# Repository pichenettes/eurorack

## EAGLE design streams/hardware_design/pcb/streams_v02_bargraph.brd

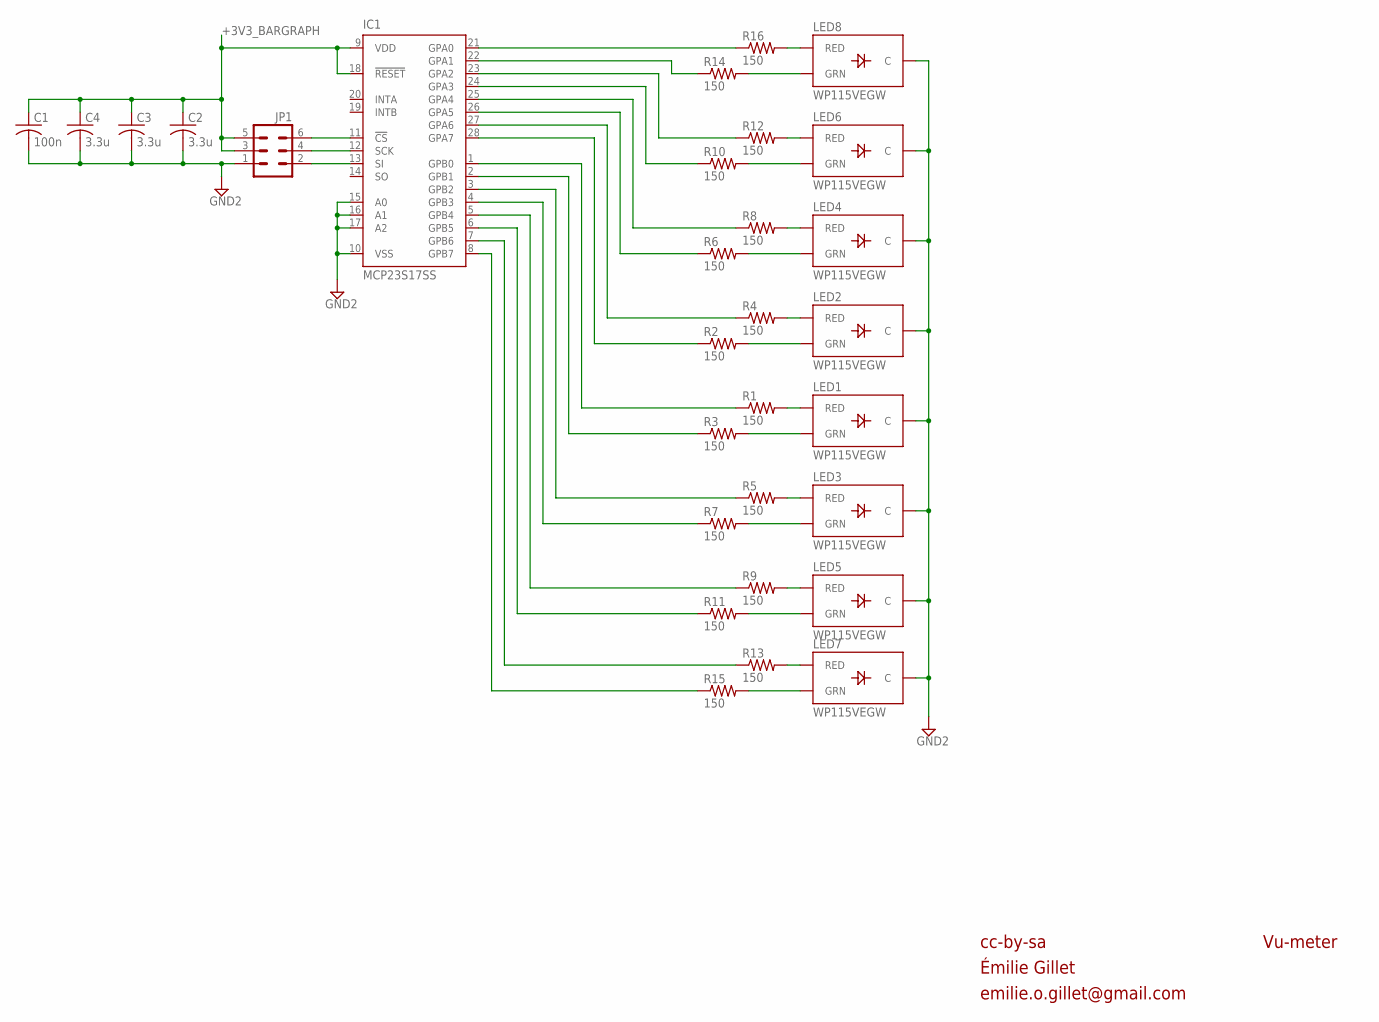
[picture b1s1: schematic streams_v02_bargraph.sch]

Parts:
C1: 100n; C0603
C2, C3, C4: 3.3u; C0603
IC1: MCP23S17SS; SSOP28
JP1: M03X2; 2X3
LED1, LED2, LED3, LED4, LED5, LED6, LED7, LED8: WP115VEGW; LED-BICOLOR-THROUGHHOLE
R1, R2, R3, R4, R5, R6, R7, R8, R9, R10, R11, R12, R13, R14, R15, R16: 150; R0603

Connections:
+3V3_BARGRAPH: C1.1, C2.1, C3.1, C4.1, IC1.9 (VDD), IC1.18 (!RESET), JP1.3, JP1.5
GND2: C1.2, C2.2, C3.2, C4.2, IC1.10 (VSS), IC1.15 (A0), IC1.16 (A1), IC1.17 (A2), JP1.1, LED1.2 (C), LED2.2 (C), LED3.2 (C), LED4.2 (C), LED5.2 (C), LED6.2 (C), LED7.2 (C), LED8.2 (C)
unnamed: IC1.11 (!CS), JP1.6
unnamed: IC1.12 (SCK), JP1.4
unnamed: LED1.3 (RED), R1.2
unnamed: IC1.13 (SI), JP1.2
unnamed: LED1.1 (GRN), R3.2
unnamed: LED3.3 (RED), R5.2
unnamed: LED3.1 (GRN), R7.2
unnamed: LED5.3 (RED), R9.2
unnamed: LED5.1 (GRN), R11.2
unnamed: LED7.3 (RED), R13.2
unnamed: LED7.1 (GRN), R15.2
unnamed: LED8.3 (RED), R16.2
unnamed: LED8.1 (GRN), R14.2
unnamed: LED6.3 (RED), R12.2
unnamed: LED6.1 (GRN), R10.2
unnamed: LED4.3 (RED), R8.2
unnamed: LED4.1 (GRN), R6.2
unnamed: LED2.3 (RED), R4.2
unnamed: LED2.1 (GRN), R2.2
unnamed: IC1.27 (GPA6), R4.1
unnamed: IC1.28 (GPA7), R2.1
unnamed: IC1.1 (GPB0), R1.1
unnamed: IC1.2 (GPB1), R3.1
unnamed: IC1.21 (GPA0), R16.1
unnamed: IC1.22 (GPA1), R14.1
unnamed: IC1.23 (GPA2), R12.1
unnamed: IC1.24 (GPA3), R10.1
unnamed: IC1.25 (GPA4), R8.1
unnamed: IC1.26 (GPA5), R6.1
unnamed: IC1.3 (GPB2), R5.1
unnamed: IC1.4 (GPB3), R7.1
unnamed: IC1.5 (GPB4), R9.1
unnamed: IC1.6 (GPB5), R11.1
unnamed: IC1.7 (GPB6), R13.1
unnamed: IC1.8 (GPB7), R15.1

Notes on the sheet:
cc-by-sa
Vu-meter
Émilie Gillet
emilie.o.gillet@gmail.com

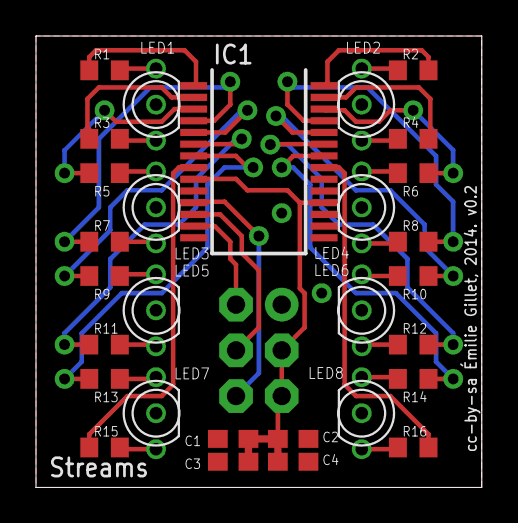
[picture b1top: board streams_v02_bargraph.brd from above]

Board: 2 copper layers, 24.8 x 25.1 mm, 30 parts (1 on the bottom side), 37 nets.

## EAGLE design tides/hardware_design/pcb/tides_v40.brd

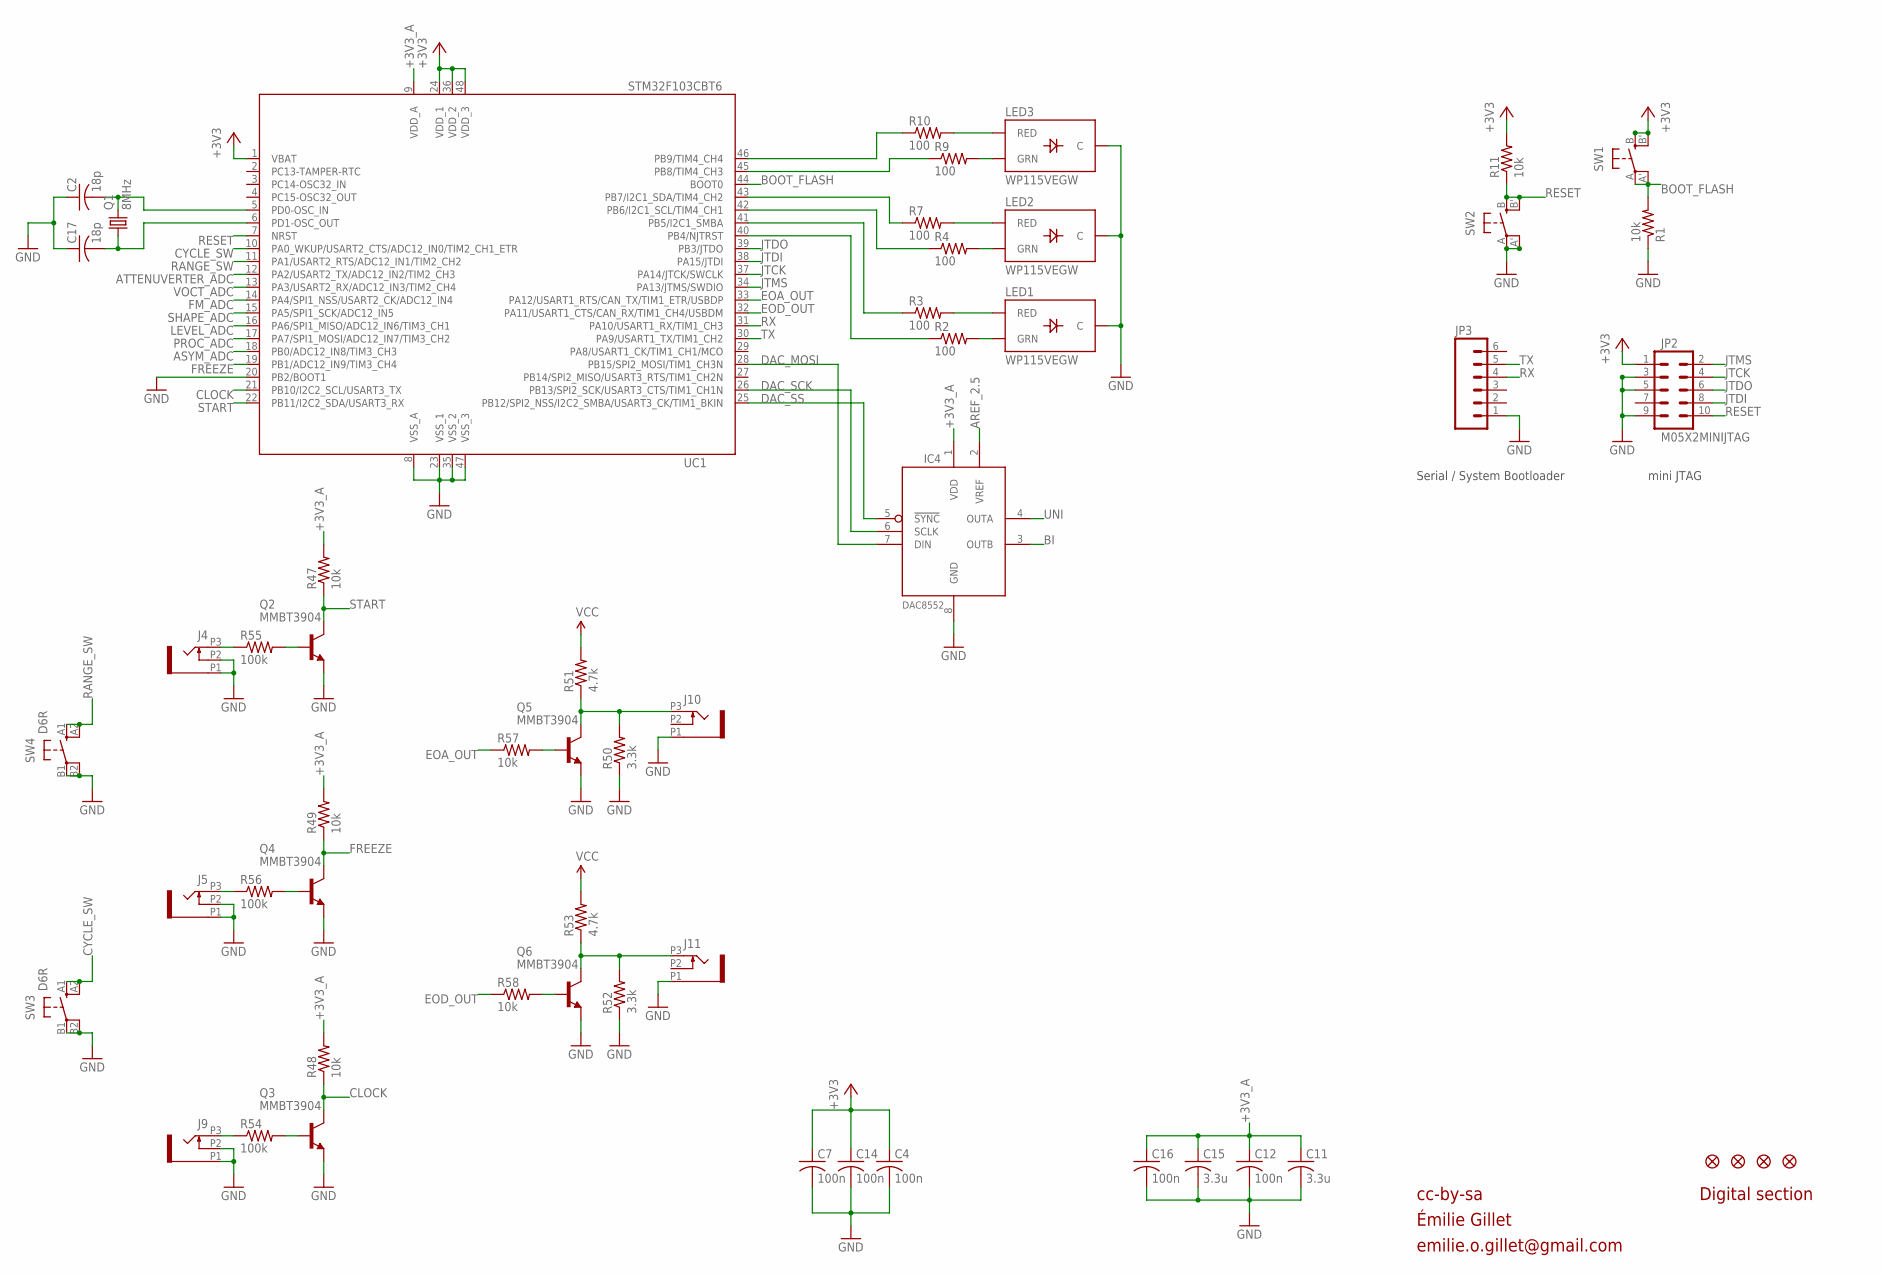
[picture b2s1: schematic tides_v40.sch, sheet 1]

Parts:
C2, C17: 18p; C0603
C4, C7, C12, C14, C16: 100n; C0603
C11, C15: 3.3u; C0603
IC4: DAC8552; MSOP-8
J4, J5, J9, J10, J11: PJ301_THONKICONN6; WQP_PJ_301M6
JP2: M05X2MINIJTAG; 2X5-1.27
JP3: M06SIP; 1X06
JP4, JP5, JP6, JP7: FIDUCIAL1X2; FIDUCIAL-1X2
LED1, LED2, LED3: WP115VEGW; LED-BICOLOR-THROUGHHOLE
Q1: 8MHz; HC49UP
Q2, Q3, Q4, Q5, Q6: MMBT3904; SOT23-BEC
R1, R11, R47, R48, R49, R57, R58: 10k; R0603
R2, R3, R4, R7, R9, R10: 100; R0603
R50, R52: 3.3k; R0603
R51, R53: 4.7k; R0603
R54, R55, R56: 100k; R0603
SW1, SW2: EVQQ2; EVQ-Q2
SW3, SW4: D6R
UC1: STM32F103CBT6; LQFP48

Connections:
+3V3: C4.1, C7.1, C14.1, JP2.1, R11.2, SW1.B (S), SW1.B' (S1), UC1.1 (VBAT), UC1.24 (VDD_1), UC1.36 (VDD_2), UC1.48 (VDD_3); also elsewhere on the board
+3V3_A: C11.1, C12.1, C15.1, C16.1, IC4.1 (VDD), R47.2, R48.2, R49.2, UC1.9 (VDD_A); also elsewhere on the board
AREF_2.5: IC4.2 (VREF); also elsewhere on the board
ASYM_ADC: UC1.18 (PB0/ADC12_IN8/TIM3_CH3); also elsewhere on the board
ATTENUVERTER_ADC: UC1.12 (PA2/USART2_TX/ADC12_IN2/TIM2_CH3); also elsewhere on the board
BI: IC4.3 (OUTB); also elsewhere on the board
BOOT_FLASH: R1.2, SW1.A, SW1.A' (P1), UC1.44 (BOOT0)
CLOCK: Q3.C, R48.1, UC1.21 (PB10/I2C2_SCL/USART3_TX)
CYCLE_SW: SW3.A1 (S), SW3.A2 (S1), UC1.10 (PA0_WKUP/USART2_CTS/ADC12_IN0/TIM2_CH1_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)
DAC_MOSI: IC4.7 (DIN), UC1.28 (PB15/SPI2_MOSI/TIM1_CH3N)
DAC_SCK: IC4.6 (SCLK), UC1.26 (PB13/SPI2_SCK/USART3_CTS/TIM1_CH1N)
DAC_SS: IC4.5 (!SYNC), UC1.25 (PB12/SPI2_NSS/I2C2_SMBA/USART3_CK/TIM1_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)
EOA_OUT: R57.1, UC1.33 (PA12/USART1_RTS/CAN_TX/TIM1_ETR/USBDP)
EOD_OUT: R58.1, UC1.32 (PA11/USART1_CTS/CAN_RX/TIM1_CH4/USBDM)
FM_ADC: UC1.14 (PA4/SPI1_NSS/USART2_CK/ADC12_IN4); also elsewhere on the board
FREEZE: Q4.C, R49.1, UC1.19 (PB1/ADC12_IN9/TIM3_CH4)
GND: C2.1, C4.2, C7.2, C11.2, C12.2, C14.2, C15.2, C16.2, C17.1, IC4.8 (GND), J4.P1 (1), J4.P2 (2), J5.P1 (1), J5.P2 (2), J9.P1 (1), J9.P2 (2), J10.P1 (1), J11.P1 (1), JP2.3, JP2.5, JP2.9, JP3.1, LED1.2 (C), LED2.2 (C), LED3.2 (C), Q2.E, Q3.E, Q4.E, Q5.E, Q6.E, R1.1, R50.1, R52.1, SW2.A, SW2.A' (P1), SW3.B1, SW3.B2 (P1), SW4.B1, SW4.B2 (P1), UC1.8 (VSS_A), UC1.20 (PB2/BOOT1), UC1.23 (VSS_1), UC1.35 (VSS_2), UC1.47 (VSS_3); also elsewhere on the board
JTCK: JP2.4, UC1.37 (PA14/JTCK/SWCLK)
JTDI: JP2.8, UC1.38 (PA15/JTDI)
JTDO: JP2.6, UC1.39 (PB3/JTDO)
JTMS: JP2.2, UC1.34 (PA13/JTMS/SWDIO)
LEVEL_ADC: UC1.16 (PA6/SPI1_MISO/ADC12_IN6/TIM3_CH1); also elsewhere on the board
unnamed: C2.2, Q1.2, UC1.5 (PD0-OSC_IN)
unnamed: C17.2, Q1.1, UC1.6 (PD1-OSC_OUT)
unnamed: J5.P3 (3), R56.1
unnamed: Q4.B, R56.2
unnamed: J9.P3 (3), R54.1
unnamed: Q3.B, R54.2
unnamed: Q6.B, R58.2
unnamed: J11.P3 (3), Q6.C, R52.2, R53.1
unnamed: LED3.3 (RED), R10.2
unnamed: LED3.1 (GRN), R9.2
unnamed: LED2.3 (RED), R7.2
unnamed: LED2.1 (GRN), R4.2
unnamed: LED1.3 (RED), R3.2
unnamed: LED1.1 (GRN), R2.2
unnamed: R10.1, UC1.46 (PB9/TIM4_CH4)
unnamed: R9.1, UC1.45 (PB8/TIM4_CH3)
unnamed: R7.1, UC1.43 (PB7/I2C1_SDA/TIM4_CH2)
unnamed: R4.1, UC1.42 (PB6/I2C1_SCL/TIM4_CH1)
unnamed: R3.1, UC1.41 (PB5/I2C1_SMBA)
unnamed: R2.1, UC1.40 (PB4/NJTRST)
unnamed: J10.P3 (3), Q5.C, R50.2, R51.1
unnamed: Q5.B, R57.2
unnamed: J4.P3 (3), R55.1
unnamed: Q2.B, R55.2
PROC_ADC: UC1.17 (PA7/SPI1_MOSI/ADC12_IN7/TIM3_CH2); also elsewhere on the board
RANGE_SW: SW4.A1 (S), SW4.A2 (S1), UC1.11 (PA1/USART2_RTS/ADC12_IN1/TIM2_CH2)
RESET: JP2.10, R11.1, SW2.B (S), SW2.B' (S1), UC1.7 (NRST)
RX: JP3.4, UC1.31 (PA10/USART1_RX/TIM1_CH3)
SHAPE_ADC: UC1.15 (PA5/SPI1_SCK/ADC12_IN5); also elsewhere on the board
START: Q2.C, R47.1, UC1.22 (PB11/I2C2_SDA/USART3_RX)
TX: JP3.5, UC1.30 (PA9/USART1_TX/TIM1_CH2)
UNI: IC4.4 (OUTA); also elsewhere on the board
VCC: R51.2, R53.2; also elsewhere on the board
VOCT_ADC: UC1.13 (PA3/USART2_RX/ADC12_IN3/TIM2_CH4); also elsewhere on the board

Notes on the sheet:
cc-by-sa
Digital section
Serial / System Bootloader
mini JTAG
Émilie Gillet
emilie.o.gillet@gmail.com

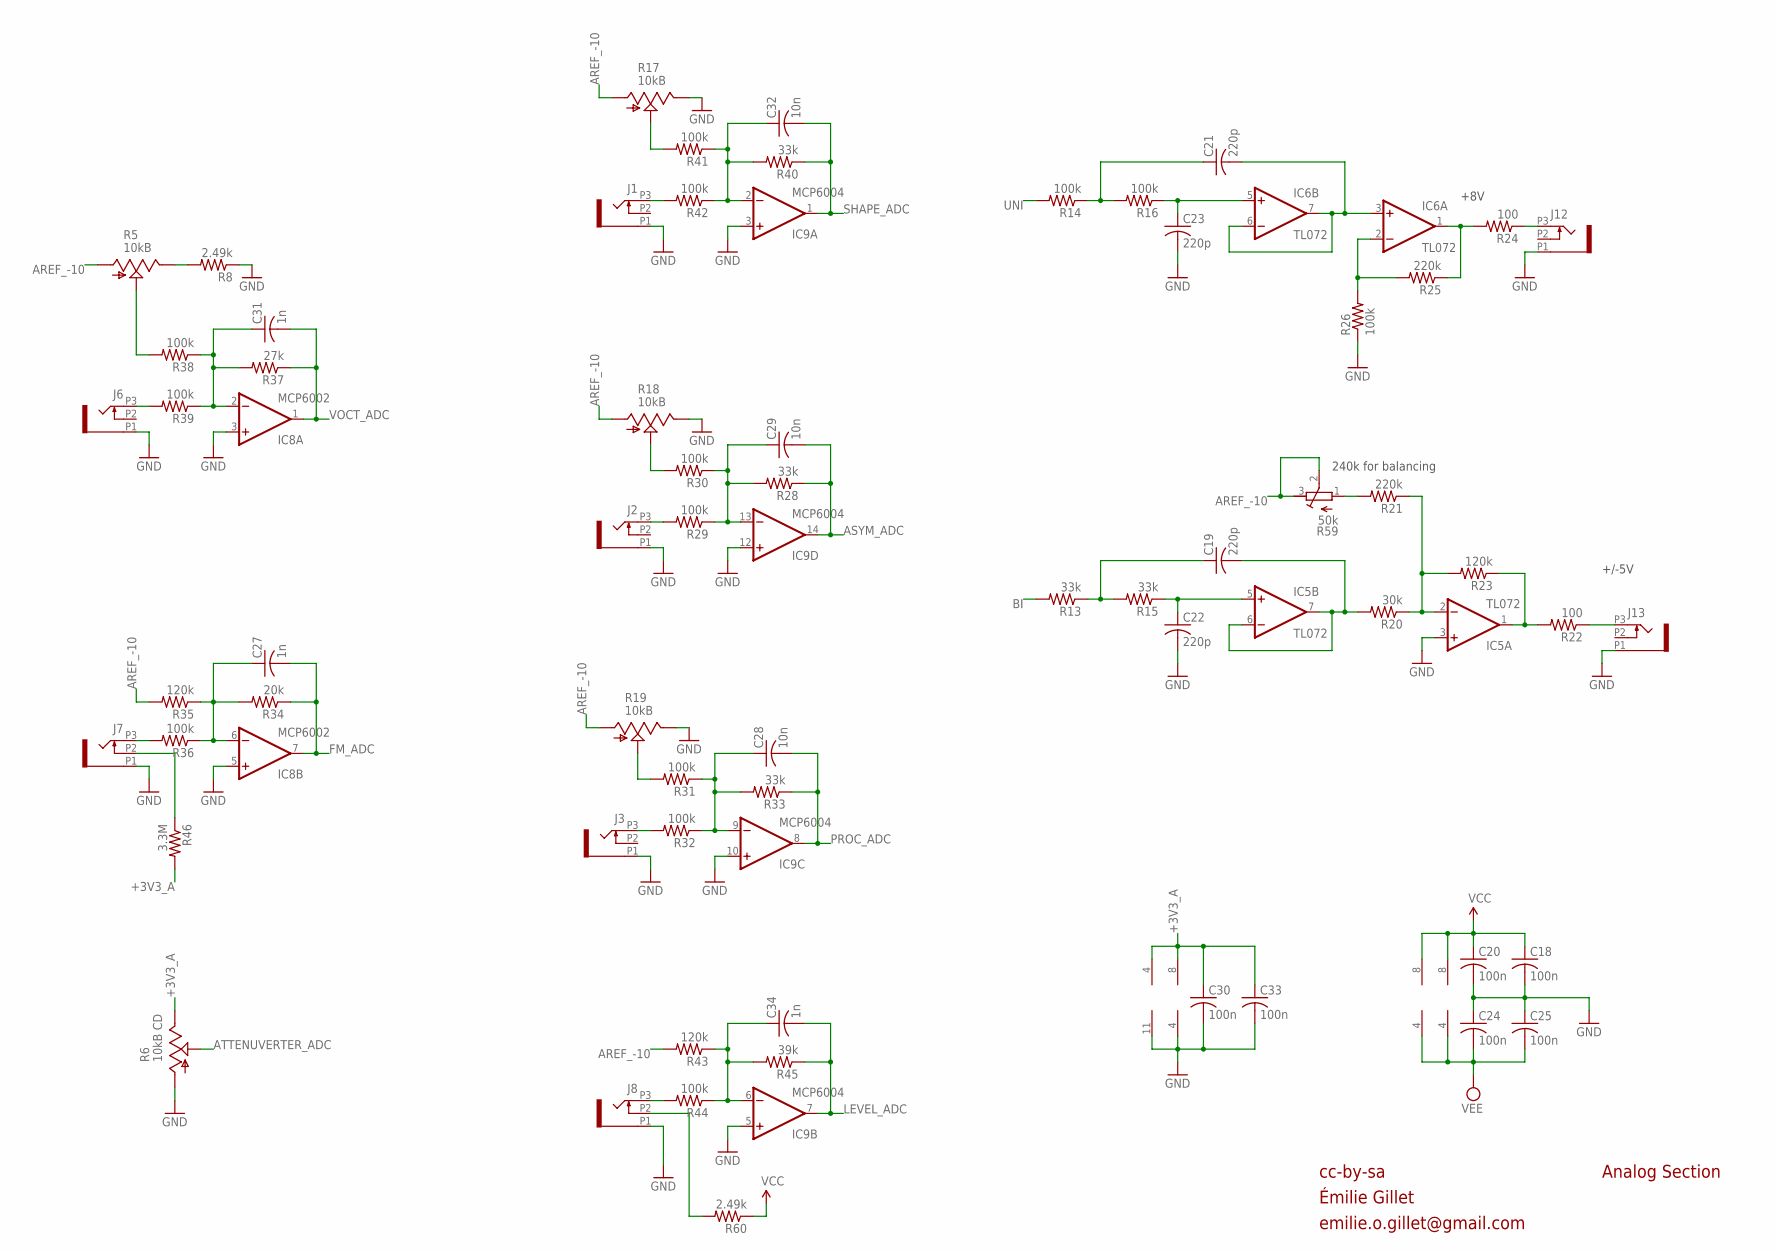
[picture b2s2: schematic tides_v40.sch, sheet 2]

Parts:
C18, C20, C24, C25, C30, C33: 100n; C0603
C19, C21, C22, C23: 220p; C0603
C27, C31, C34: 1n; C0603
C28, C29, C32: 10n; C0603
IC5, IC6: TL072; SO08
IC8: MCP6002; SO08
IC9: MCP6004; SO14
J1, J2, J3, J6, J7, J8, J12, J13: PJ301_THONKICONN6; WQP_PJ_301M6
R5, R17, R18, R19: 10kB; ALPS_POT_VERTICAL_PS
R6: 10kB CD; ALPS_POT_VERTICAL_PS
R8: 2.49k; R0603
R13, R15, R28, R33, R40: 33k; R0603
R14, R16, R26, R29, R30, R31, R32, R36, R38, R39, R41, R42, R44: 100k; R0603
R20: 30k; R0603
R21, R25: 220k; R0603
R22, R24: 100; R0603
R23, R35, R43: 120k; R0603
R34: 20k; R0603
R37: 27k; R0603
R45: 39k; R0603
R46: 3.3M; R0603
R59: 50k; RTRIM3296X
R60: 2.49k; R0805

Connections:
+3V3_A: C30.1, C33.1, IC8.8 (V+), IC9.4 (V+), R6.P$1 (E), R46.2; also elsewhere on the board
AREF_-10: R5.P$3 (A), R17.P$3 (A), R18.P$3 (A), R19.P$3 (A), R35.2, R43.2, R59.2 (S), R59.3 (A); also elsewhere on the board
ASYM_ADC: C29.2, IC9.14 (OUT), R28.1; also elsewhere on the board
ATTENUVERTER_ADC: R6.P$2 (S); also elsewhere on the board
BI: R13.2; also elsewhere on the board
BI_OUT: IC5.1 (OUT), R22.2, R23.1
FM_ADC: C27.2, IC8.7 (OUT), R34.1; also elsewhere on the board
F_CV: IC5.2 (-IN), R20.1, R21.1, R23.2
GND: C18.2, C20.2, C22.2, C23.2, C24.1, C25.1, C30.2, C33.2, IC5.3 (+IN), IC8.3 (+IN), IC8.4 (V-), IC8.5 (+IN), IC9.3 (+IN), IC9.5 (+IN), IC9.10 (+IN), IC9.11 (V-), IC9.12 (+IN), J1.P1 (1), J2.P1 (1), J3.P1 (1), J6.P1 (1), J7.P1 (1), J8.P1 (1), J12.P1 (1), J13.P1 (1), R6.P$3 (A), R8.1, R17.P$1 (E), R18.P$1 (E), R19.P$1 (E), R26.1; also elsewhere on the board
LEVEL_ADC: C34.2, IC9.7 (OUT), R45.1; also elsewhere on the board
unnamed: J1.P3 (3), R42.2
unnamed: C32.1, IC9.2 (-IN), R40.2, R41.1, R42.1
unnamed: R17.P$2 (S), R41.2
unnamed: J2.P3 (3), R29.2
unnamed: C29.1, IC9.13 (-IN), R28.2, R29.1, R30.1
unnamed: J7.P2 (2), R46.1
unnamed: R18.P$2 (S), R30.2
unnamed: J3.P3 (3), R32.2
unnamed: C28.1, IC9.9 (-IN), R31.1, R32.1, R33.2
unnamed: R19.P$2 (S), R31.2
unnamed: J8.P3 (3), R44.2
unnamed: C34.1, IC9.6 (-IN), R43.1, R44.1, R45.2
unnamed: J6.P3 (3), R39.2
unnamed: C31.1, IC8.2 (-IN), R37.2, R38.1, R39.1
unnamed: R5.P$2 (S), R38.2
unnamed: J13.P3 (3), R22.1
unnamed: R5.P$1 (E), R8.2
unnamed: J7.P3 (3), R36.2
unnamed: C27.1, IC8.6 (-IN), R34.2, R35.1, R36.1
unnamed: R21.2, R59.1 (E)
unnamed: IC6.2 (-IN), R25.2, R26.2
unnamed: C19.2, IC5.6 (-IN), IC5.7 (OUT), R20.2
unnamed: C22.1, IC5.5 (+IN), R15.1
unnamed: C19.1, R13.1, R15.2
unnamed: IC6.1 (OUT), R24.2, R25.1
unnamed: J8.P2 (2), R60.2
unnamed: C21.2, IC6.3 (+IN), IC6.6 (-IN), IC6.7 (OUT)
unnamed: C23.1, IC6.5 (+IN), R16.1
unnamed: C21.1, R14.1, R16.2
PROC_ADC: C28.2, IC9.8 (OUT), R33.1; also elsewhere on the board
SHAPE_ADC: C32.2, IC9.1 (OUT), R40.1; also elsewhere on the board
UNI: R14.2; also elsewhere on the board
UNI_OUT: J12.P3 (3), R24.1
VCC: C18.1, C20.1, IC5.8 (V+), IC6.8 (V+), R60.1; also elsewhere on the board
VEE: C24.2, C25.2, IC5.4 (V-), IC6.4 (V-); also elsewhere on the board
VOCT_ADC: C31.2, IC8.1 (OUT), R37.1; also elsewhere on the board

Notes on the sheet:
cc-by-sa
Analog Section
+8V
+/-5V
240k for balancing
Émilie Gillet
emilie.o.gillet@gmail.com

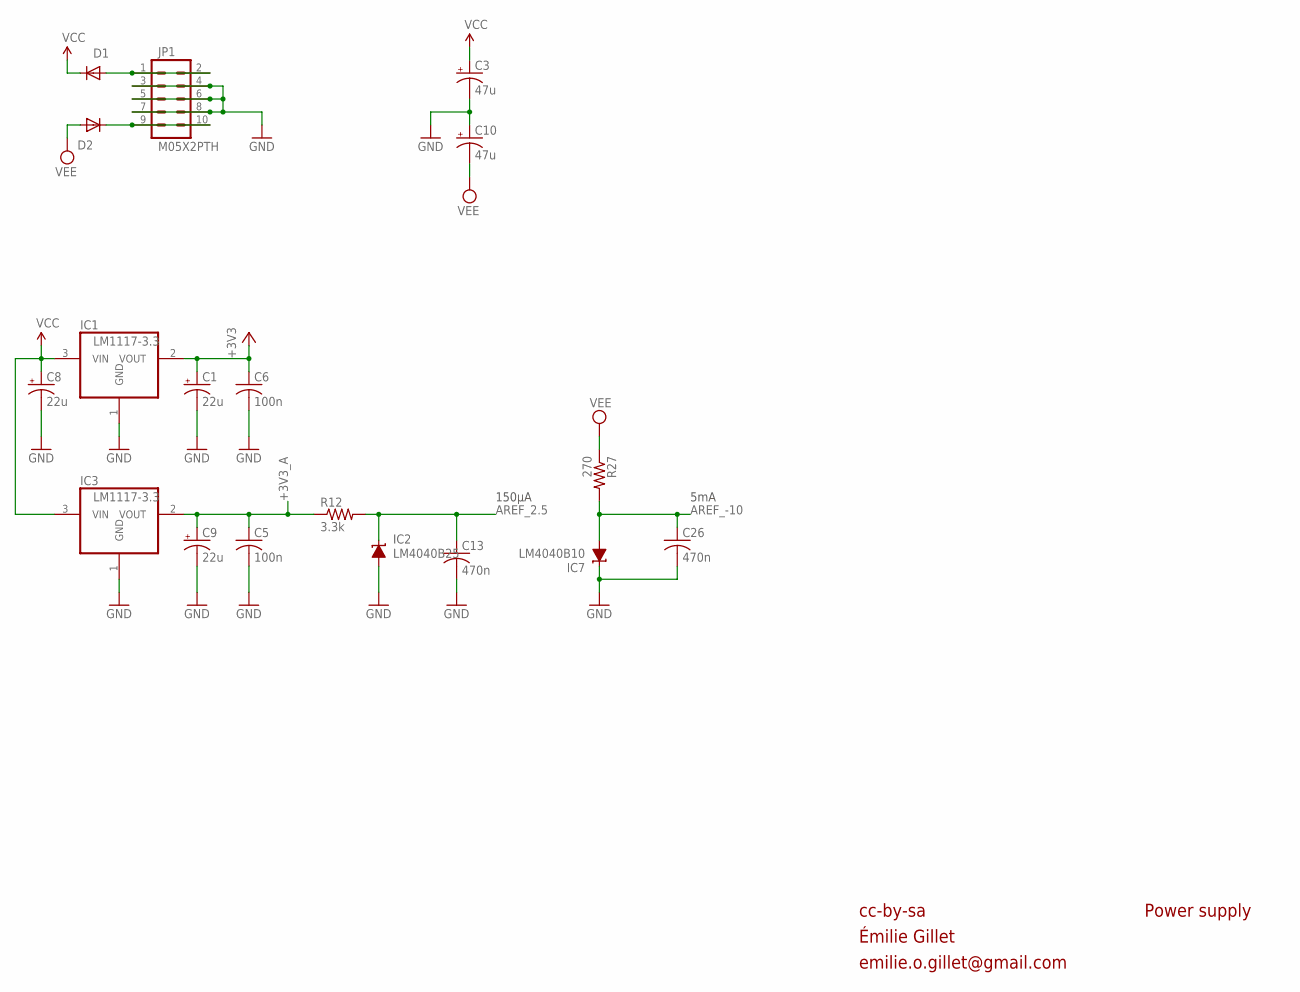
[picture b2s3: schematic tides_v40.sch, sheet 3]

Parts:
C1, C8, C9: 22u; PANASONIC_C
C3, C10: 47u; PANASONIC_D
C5, C6: 100n; C0603
C13, C26: 470n; C0603
D1, D2: 1N5819HW; SOD123
IC1, IC3: LM1117-3.3; SOT223
IC2: LM4040B25; DBZ_R-PDSO-G3
IC7: LM4040B10; DBZ_R-PDSO-G3
JP1: M05X2PTH; AVR_ICSP
R12: 3.3k; R0603
R27: 270; R0603

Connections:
+3V3: C1.+, C6.1, IC1.2 (VOUT); also elsewhere on the board
+3V3_A: C5.1, C9.+, IC3.2 (VOUT), R12.1; also elsewhere on the board
AREF_2.5: C13.1, IC2.1 (C), R12.2; also elsewhere on the board
AREF_-10: C26.1, IC7.2 (A), R27.2; also elsewhere on the board
GND: C1.-, C3.-, C5.2, C6.2, C8.-, C9.-, C10.+, C13.2, C26.2, IC1.1 (GND), IC2.2 (A), IC3.1 (GND), IC7.1 (C), JP1.3, JP1.4, JP1.5, JP1.6, JP1.7, JP1.8; also elsewhere on the board
unnamed: D1.A, JP1.1, JP1.2
unnamed: D2.C, JP1.9, JP1.10
VCC: C3.+, C8.+, D1.C, IC1.3 (VIN), IC3.3 (VIN); also elsewhere on the board
VEE: C10.-, D2.A, R27.1; also elsewhere on the board

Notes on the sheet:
cc-by-sa
Power supply
5mA
150µA
Émilie Gillet
emilie.o.gillet@gmail.com

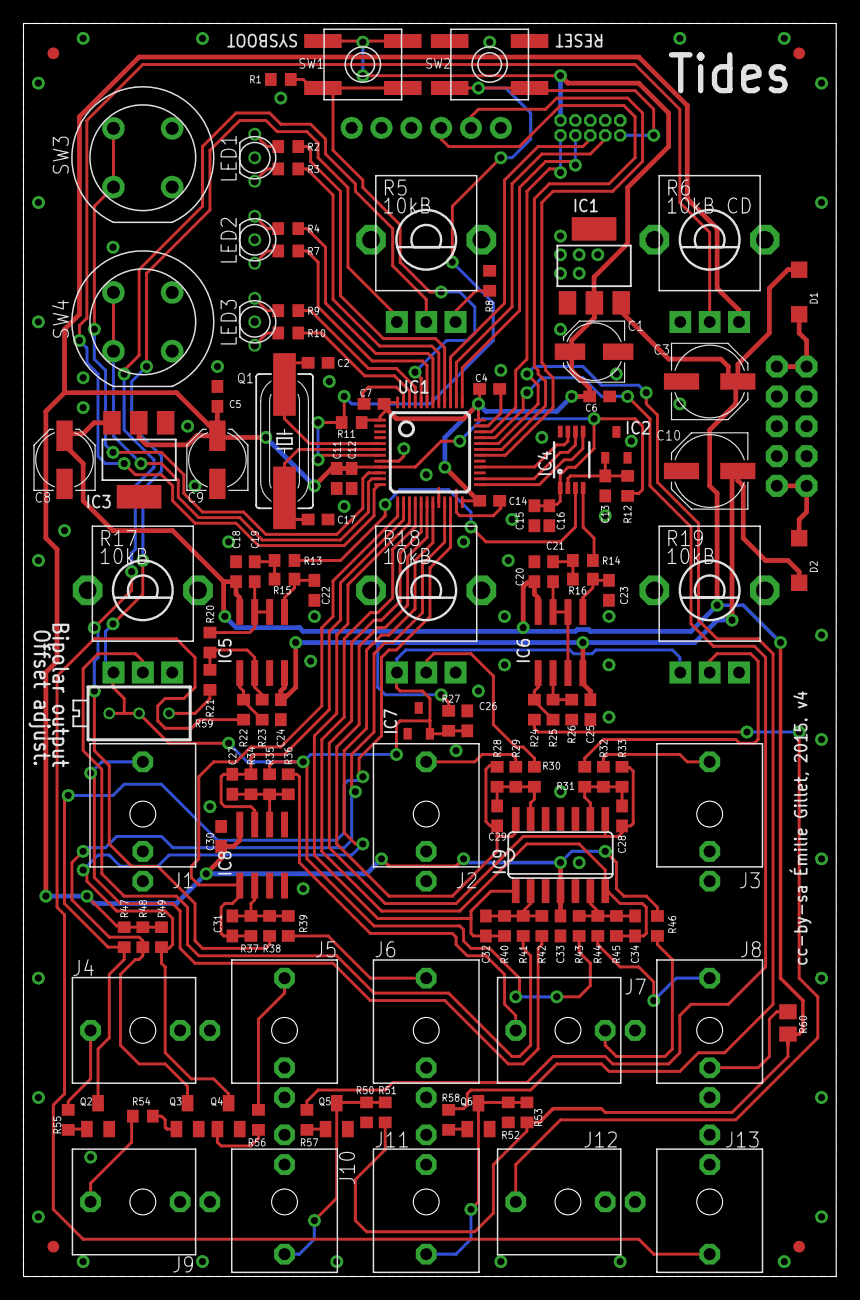
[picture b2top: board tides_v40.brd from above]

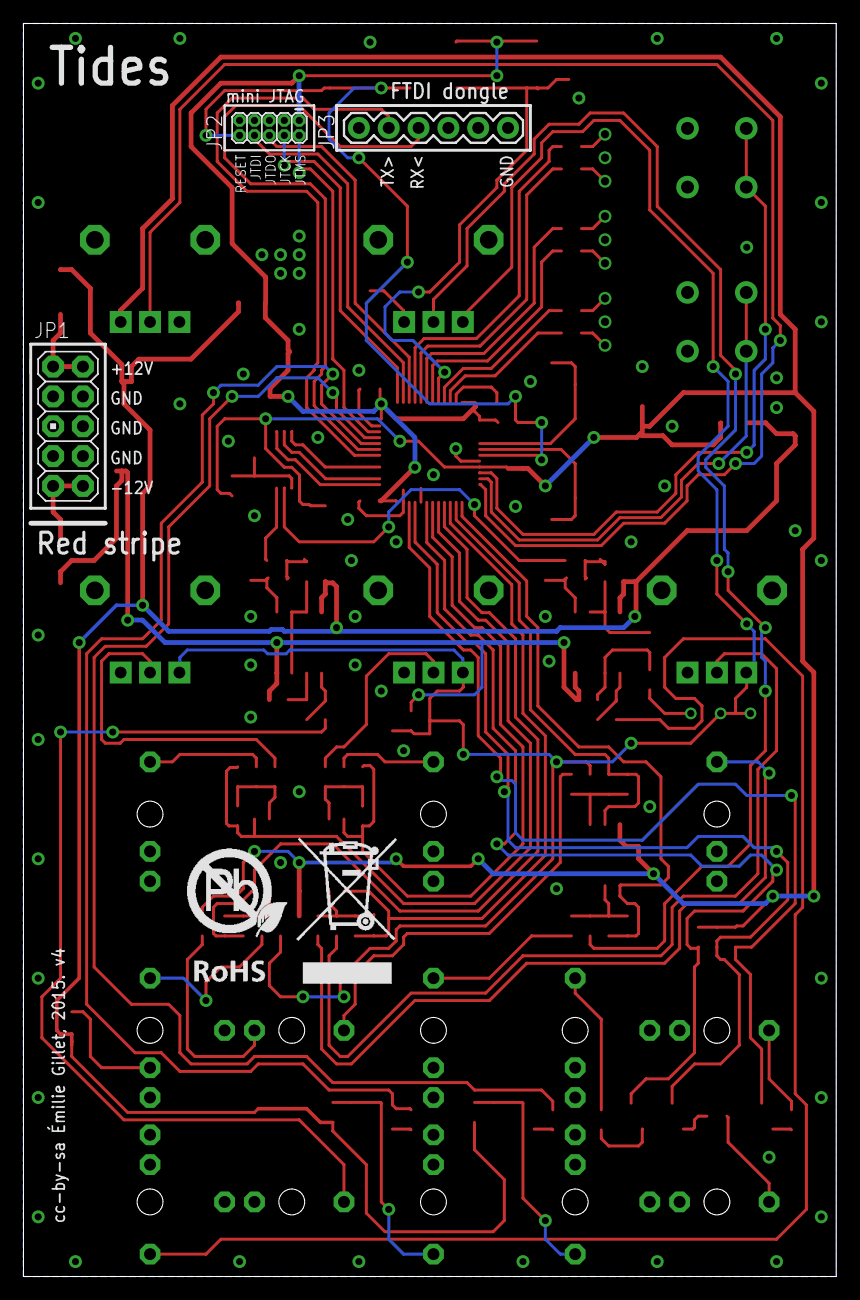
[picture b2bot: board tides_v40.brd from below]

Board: 2 copper layers, 69.2 x 106.7 mm, 140 parts (4 on the bottom side), 92 nets.

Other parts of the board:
U$3: ROHS_BIG

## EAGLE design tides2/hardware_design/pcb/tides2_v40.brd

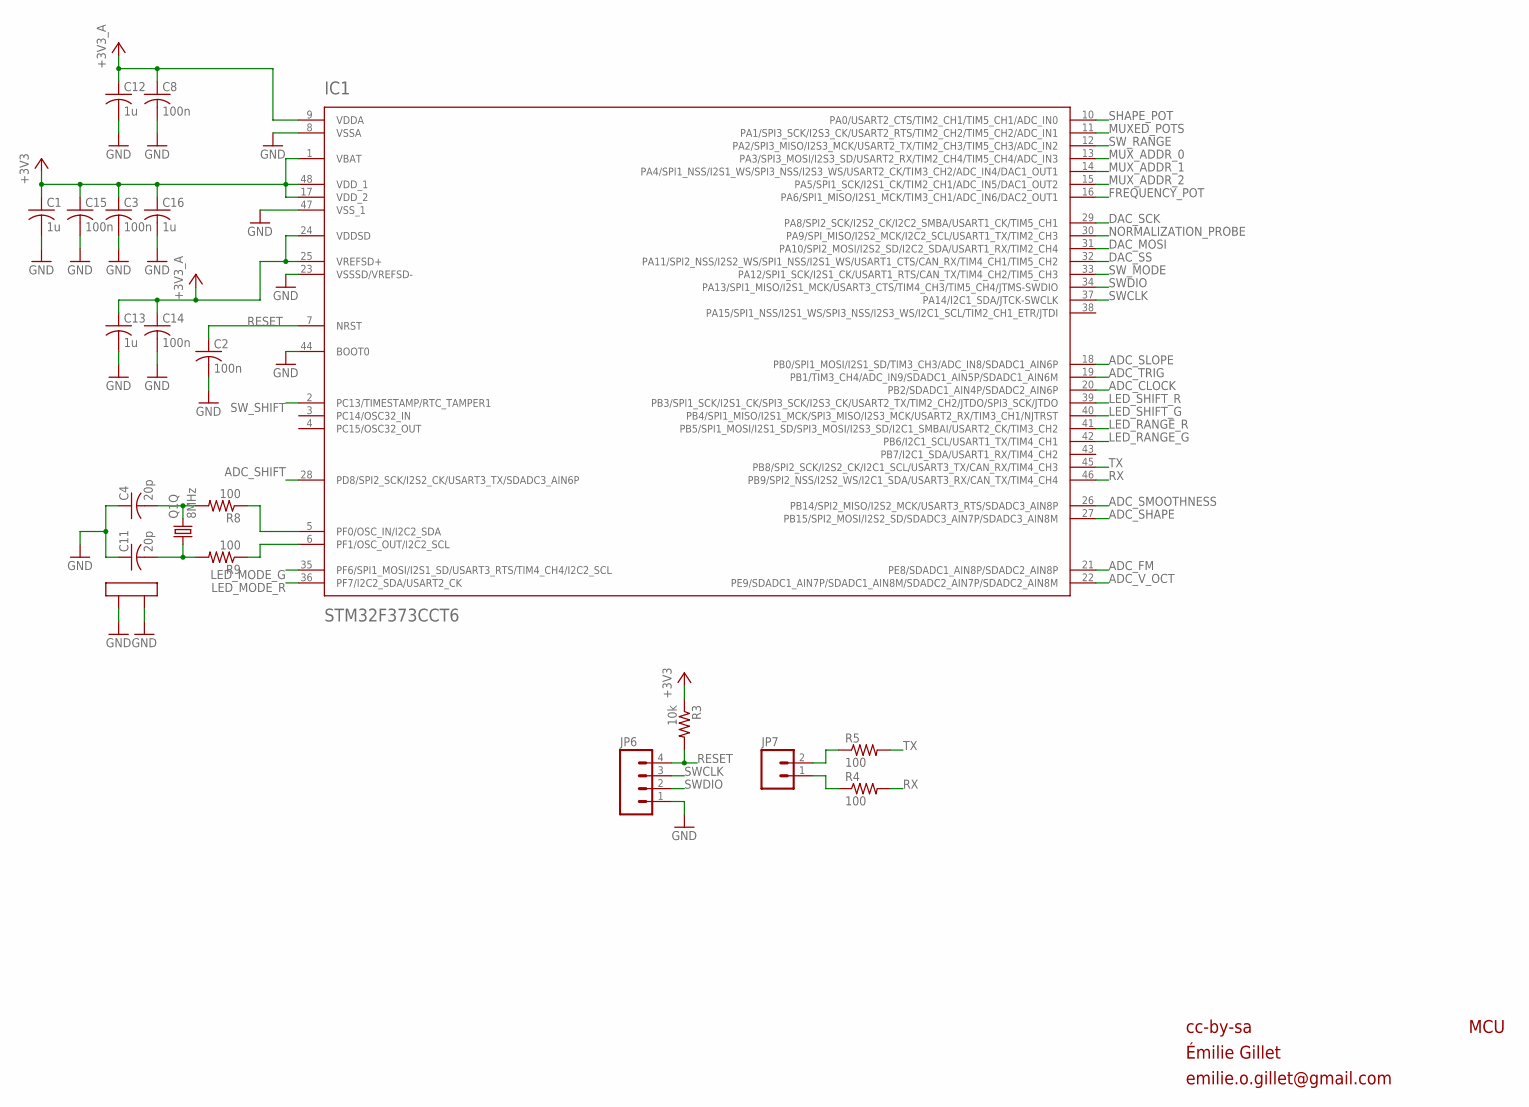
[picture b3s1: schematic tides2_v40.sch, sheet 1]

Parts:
C1, C12, C13, C16: 1u; C0402
C2, C3, C8, C14, C15: 100n; C0402
C4, C11: 20p; C0402
IC1: STM32F373CCT6; LQFP48
JP6: M04PTH; 1X04
JP7: M02PTH; 1X02
Q1: 8MHz; CTS406
R3: 10k; R0402
R4, R5, R8, R9: 100; R0402

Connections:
+3V3: C1.1, C3.1, C15.1, C16.1, IC1.1 (VBAT), IC1.17 (VDD_2), IC1.48 (VDD_1), R3.1; also elsewhere on the board
+3V3_A: C8.1, C12.1, C13.1, C14.1, IC1.9 (VDDA), IC1.24 (VDDSD), IC1.25 (VREFSD+); also elsewhere on the board
ADC_CLOCK: IC1.20 (PB2/SDADC1_AIN4P/SDADC2_AIN6P); also elsewhere on the board
ADC_FM: IC1.21 (PE8/SDADC1_AIN8P/SDADC2_AIN8P); also elsewhere on the board
ADC_SHAPE: IC1.27 (PB15/SPI2_MOSI/I2S2_SD/SDADC3_AIN7P/SDA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); also elsewhere on the board
ADC_SHIFT: IC1.28 (PD8/SPI2_SCK/I2S2_CK/USART3_TX/SDADC3_A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); also elsewhere on the board
ADC_SLOPE: IC1.18 (PB0/SPI1_MOSI/I2S1_SD/TIM3_CH3/ADC_IN8/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); also elsewhere on the board
ADC_SMOOTHNESS: IC1.26 (PB14/SPI2_MISO/I2S2_MCK/USART3_RTS/SDAD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); also elsewhere on the board
ADC_TRIG: IC1.19 (PB1/TIM3_CH4/ADC_IN9/SDADC1_AIN5P/SDADC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); also elsewhere on the board
ADC_V_OCT: IC1.22 (PE9/SDADC1_AIN7P/SDADC1_AIN8M/SDADC2_AI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); also elsewhere on the board
DAC_MOSI: IC1.31 (PA10/SPI2_MOSI/I2S2_SD/I2C2_SDA/USART1_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); also elsewhere on the board
DAC_SCK: IC1.29 (PA8/SPI2_SCK/I2S2_CK/I2C2_SMBA/USART1_C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); also elsewhere on the board
DAC_SS: IC1.32 (PA11/SPI2_NSS/I2S2_WS/SPI1_NSS/I2S1_WS/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); also elsewhere on the board
FREQUENCY_POT: IC1.16 (PA6/SPI1_MISO/I2S1_MCK/TIM3_CH1/ADC_IN6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); also elsewhere on the board
GND: C1.2, C2.2, C3.2, C4.1, C8.2, C11.1, C12.2, C13.2, C14.2, C15.2, C16.2, IC1.8 (VSSA), IC1.23 (VSSSD/VREFSD-), IC1.44 (BOOT0), IC1.47 (VSS_1), JP6.1, Q1.2 (LID1), Q1.4 (LID2); also elsewhere on the board
LED_MODE_G: IC1.35 (PF6/SPI1_MOSI/I2S1_SD/USART3_RTS/TIM4_C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); also elsewhere on the board
LED_MODE_R: IC1.36 (PF7/I2C2_SDA/USART2_CK); also elsewhere on the board
LED_RANGE_G: IC1.42 (PB6/I2C1_SCL/USART1_TX/TIM4_CH1); also elsewhere on the board
LED_RANGE_R: IC1.41 (PB5/SPI1_MOSI/I2S1_SD/SPI3_MOSI/I2S3_SD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); also elsewhere on the board
LED_SHIFT_G: IC1.40 (PB4/SPI1_MISO/I2S1_MCK/SPI3_MISO/I2S3_M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); also elsewhere on the board
LED_SHIFT_R: IC1.39 (PB3/SPI1_SCK/I2S1_CK/SPI3_SCK/I2S3_CK/U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); also elsewhere on the board
MUXED_POTS: IC1.11 (PA1/SPI3_SCK/I2S3_CK/USART2_RTS/TIM2_CH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); also elsewhere on the board
MUX_ADDR_0: IC1.13 (PA3/SPI3_MOSI/I2S3_SD/USART2_RX/TIM2_CH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); also elsewhere on the board
MUX_ADDR_1: IC1.14 (PA4/SPI1_NSS/I2S1_WS/SPI3_NSS/I2S3_WS/U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); also elsewhere on the board
MUX_ADDR_2: IC1.15 (PA5/SPI1_SCK/I2S1_CK/TIM2_CH1/ADC_IN5/D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); also elsewhere on the board
unnamed: IC1.5 (PF0/OSC_IN/I2C2_SDA), R8.1
unnamed: IC1.6 (PF1/OSC_OUT/I2C2_SCL), R9.1
unnamed: C4.2, Q1.3 (2), R8.2
unnamed: JP7.2, R5.1
unnamed: C11.2, Q1.1, R9.2
unnamed: JP7.1, R4.1
NORMALIZATION_PROBE: IC1.30 (PA9/SPI_MISO/I2S2_MCK/I2C2_SCL/USART1_T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); also elsewhere on the board
RESET: C2.1, IC1.7 (NRST), JP6.4, R3.2
RX: IC1.46 (PB9/SPI2_NSS/I2S2_WS/I2C1_SDA/USART3_RX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), R4.2
SHAPE_POT: IC1.10 (PA0/USART2_CTS/TIM2_CH1/TIM5_CH1/ADC_IN0); also elsewhere on the board
SWCLK: IC1.37 (PA14/I2C1_SDA/JTCK-SWCLK), JP6.3
SWDIO: IC1.34 (PA13/SPI1_MISO/I2S1_MCK/USART3_CTS/TIM4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), JP6.2
SW_MODE: IC1.33 (PA12/SPI1_SCK/I2S1_CK/USART1_RTS/CAN_TX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); also elsewhere on the board
SW_RANGE: IC1.12 (PA2/SPI3_MISO/I2S3_MCK/USART2_TX/TIM2_C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); also elsewhere on the board
SW_SHIFT: IC1.2 (PC13/TIMESTAMP/RTC_TAMPER1); also elsewhere on the board
TX: IC1.45 (PB8/SPI2_SCK/I2S2_CK/I2C1_SCL/USART3_TX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), R5.2

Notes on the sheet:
cc-by-sa
MCU
Émilie Gillet
emilie.o.gillet@gmail.com

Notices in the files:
tides2/hardware_design/pcb/tides2_v40.brd:
cc-by-sa Émilie Gillet
warps/hardware_design/pcb/warps_v30.brd:
cc-by-sa Émilie Gillet, 2015. v3
